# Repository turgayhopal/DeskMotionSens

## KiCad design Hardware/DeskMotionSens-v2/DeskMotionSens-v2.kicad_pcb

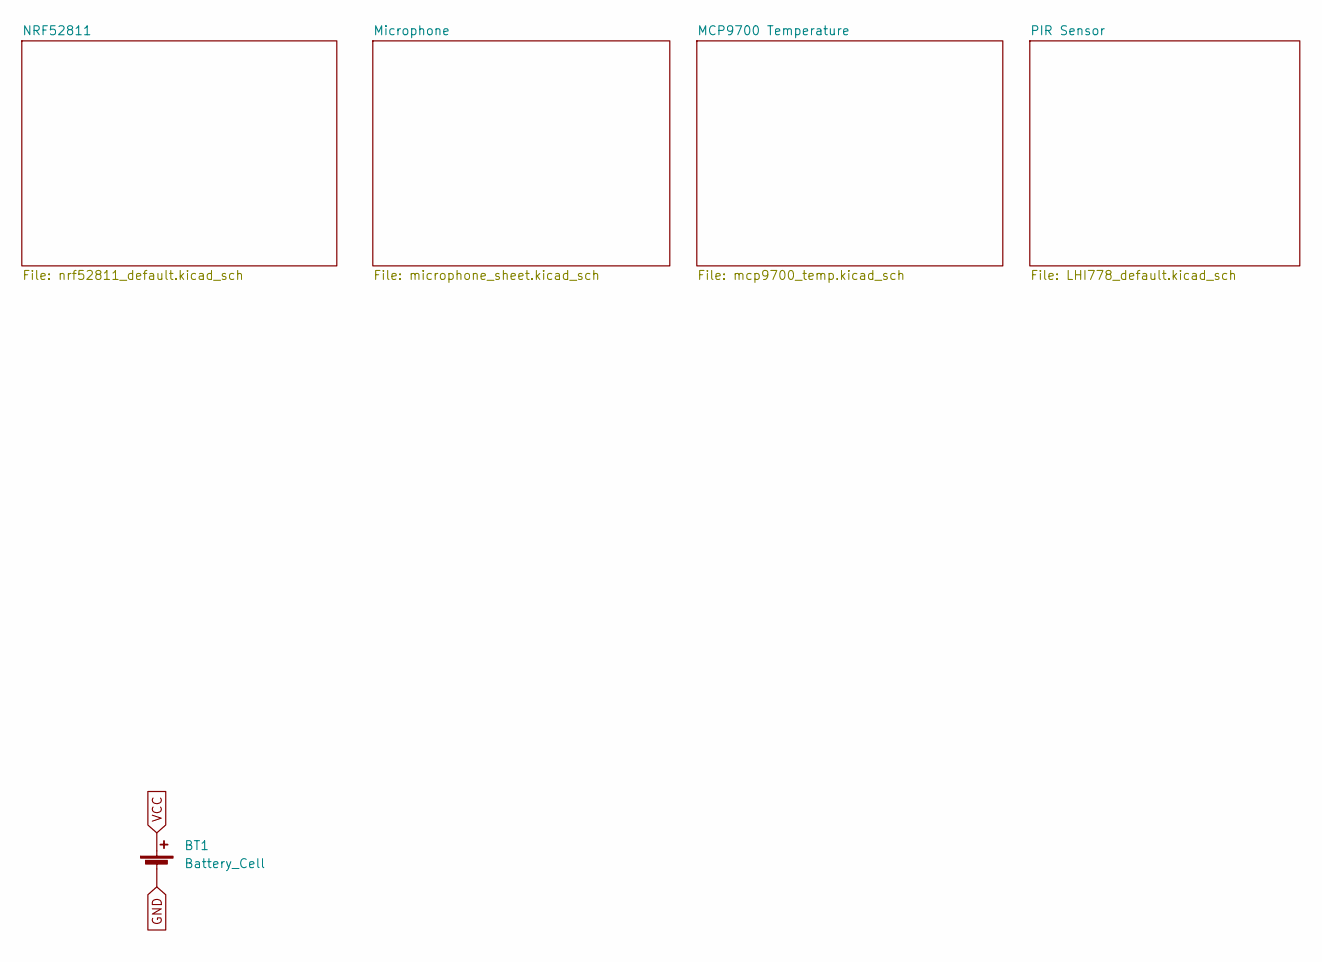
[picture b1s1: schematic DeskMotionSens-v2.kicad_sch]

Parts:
BT1: Battery_Cell; BatteryHolder_Keystone_1058_1x2032

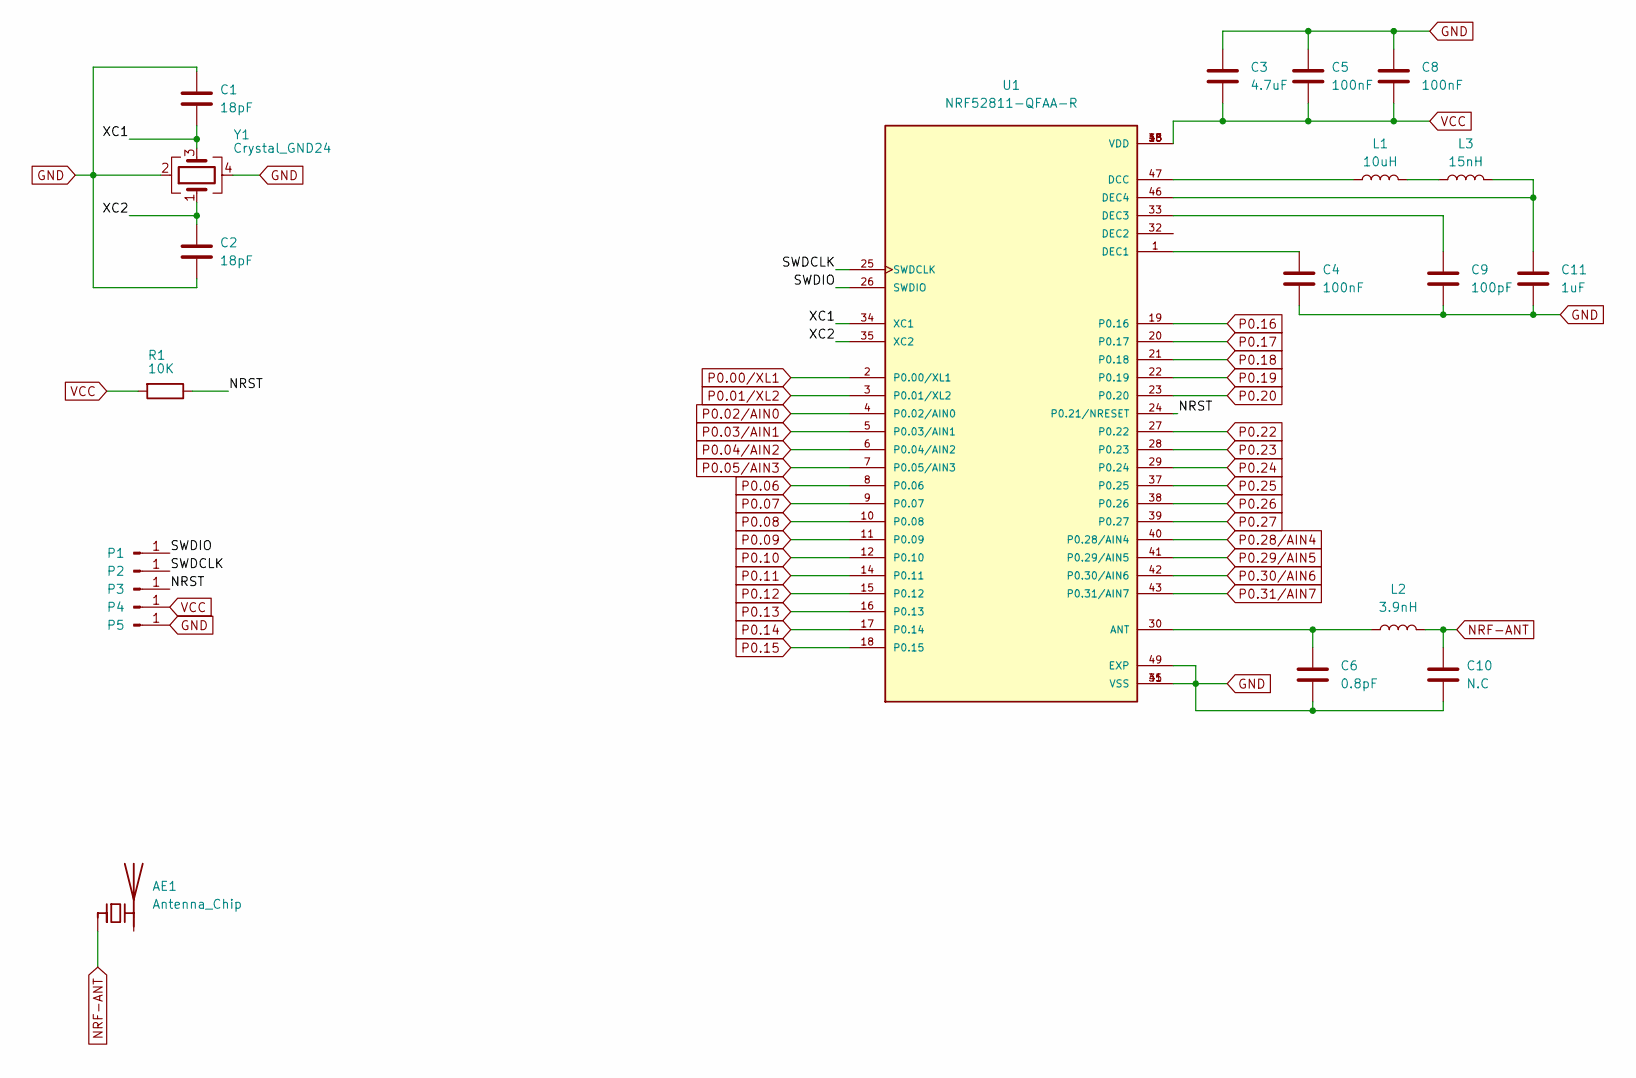
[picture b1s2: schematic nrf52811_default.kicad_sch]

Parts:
AE1: Antenna_Chip; Johanson_2450AT18x100
C1, C2: 18pF; C_0402_1005Metric
C3: 4.7uF; C_0402_1005Metric
C4, C5, C8: 100nF; C_0402_1005Metric
C6: 0.8pF; C_0402_1005Metric
C9: 100pF; C_0402_1005Metric
C10: N.C; C_0402_1005Metric
C11: 1uF; C_0402_1005Metric
L1: 10uH; C_0603_1608Metric
L2: 3.9nH; C_0603_1608Metric
L3: 15nH; C_0603_1608Metric
P1, P2, P3, P4, P5: Conn_01x01_Male; TestPoint_Pad_D1.0mm
R1: 10K; R_0402_1005Metric
U1: NRF52811-QFAA-R; QFN40P600X600X90-49N; PARTREV 1.0
Y1: Crystal_GND24; Crystal_SMD_3225-4Pin_3.2x2.5mm

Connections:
/NRF52811/NRST: P3.1, R1.1, U1.24 (P0.21/NRESET); also elsewhere on the board
/NRF52811/SWDCLK: P2.1, U1.25 (SWDCLK); also elsewhere on the board
/NRF52811/SWDIO: P1.1, U1.26 (SWDIO); also elsewhere on the board
/NRF52811/XC1: C1.1, U1.34 (XC1), Y1.3; also elsewhere on the board
/NRF52811/XC2: C2.2, U1.35 (XC2), Y1.1; also elsewhere on the board
GND: C1.2, C2.1, C3.1, C4.2, C5.1, C6.2, C8.1, C9.2, C10.2, C11.2, P5.1, U1.31 (VSS), U1.45 (VSS), U1.49 (EXP), Y1.2, Y1.4; also elsewhere on the board
NRF-ANT: AE1.1 (FEED), C10.1, L2.2
unnamed 7: C4.1, U1.1 (DEC1); also elsewhere on the board
unnamed 8: C6.1, L2.1, U1.30 (ANT); also elsewhere on the board
unnamed 9: C9.1, U1.33 (DEC3); also elsewhere on the board
unnamed 10: C11.1, L3.2, U1.46 (DEC4); also elsewhere on the board
unnamed 11: L1.1, U1.47 (DCC); also elsewhere on the board
unnamed: L1.2, L3.1
VCC: C3.2, C5.2, C8.2, P4.1, R1.2, U1.13 (VDD), U1.36 (VDD), U1.48 (VDD); also elsewhere on the board

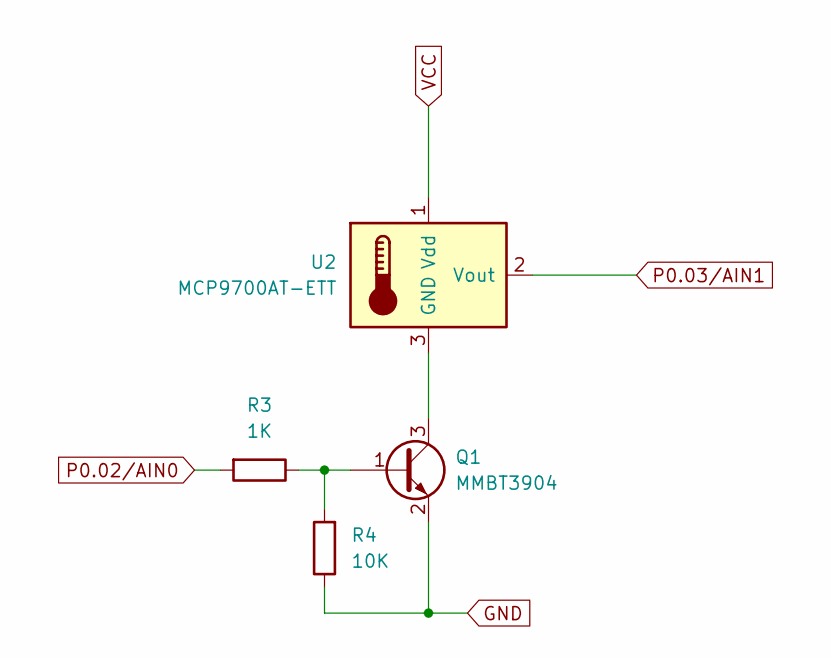
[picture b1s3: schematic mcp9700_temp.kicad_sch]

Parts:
Q1: MMBT3904; SOT-23
R3: 1K; R_0402_1005Metric
R4: 10K; R_0402_1005Metric
U2: MCP9700AT-ETT; SOT-23

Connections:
GND: Q1.2 (E), R4.1; also elsewhere on the board
unnamed: Q1.1 (B), R3.1, R4.2
unnamed: Q1.3 (C), U2.3 (GND)
P0.02/AIN0: R3.2; also elsewhere on the board
P0.03/AIN1: U2.2 (Vout); also elsewhere on the board
VCC: U2.1 (Vdd); also elsewhere on the board

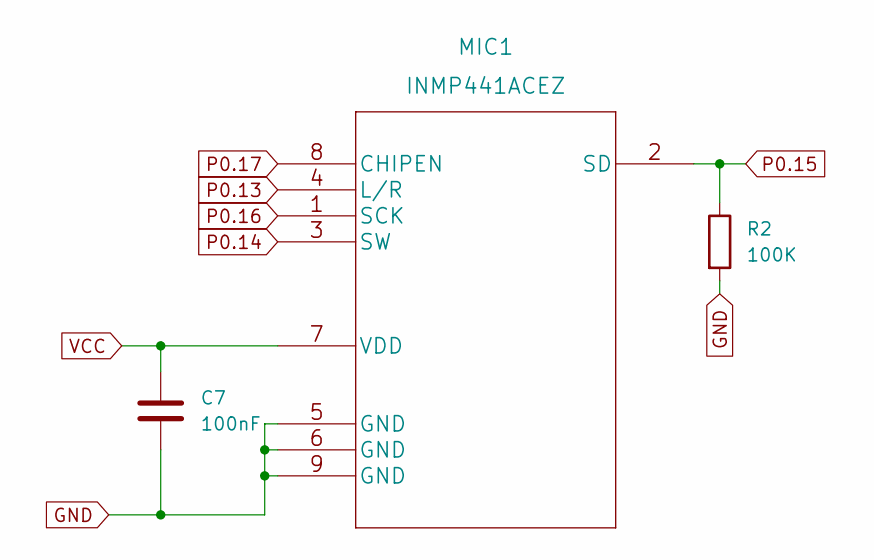
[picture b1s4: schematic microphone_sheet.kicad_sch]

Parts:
C7: 100nF; C_0402_1005Metric
MIC1: INMP441ACEZ
R2: 100K; R_0402_1005Metric

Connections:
GND: C7.1, MIC1.5 (GND), MIC1.6 (GND), MIC1.9 (GND), R2.2; also elsewhere on the board
P0.13: MIC1.4 (L/R); also elsewhere on the board
P0.14: MIC1.3 (SW); also elsewhere on the board
P0.15: MIC1.2 (SD), R2.1; also elsewhere on the board
P0.16: MIC1.1 (SCK); also elsewhere on the board
P0.17: MIC1.8 (CHIPEN); also elsewhere on the board
VCC: C7.2, MIC1.7 (VDD); also elsewhere on the board

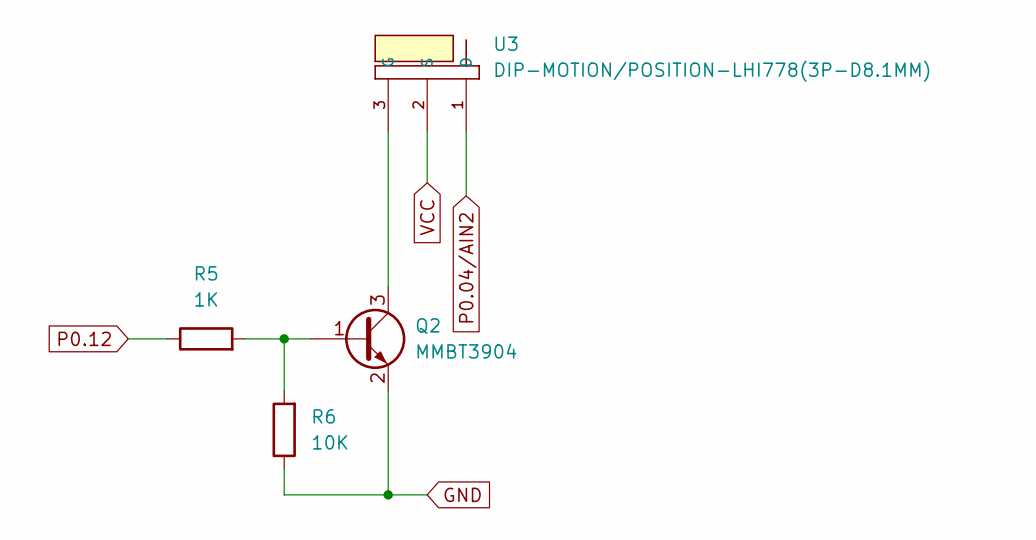
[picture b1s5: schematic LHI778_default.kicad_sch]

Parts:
Q2: MMBT3904; SOT-23
R5: 1K; R_0402_1005Metric
R6: 10K; R_0402_1005Metric
U3: DIP-MOTION/POSITION-LHI778(3P-D8.1MM); SNR3-D8.1XH4.2MM; MPN LHI778

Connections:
GND: Q2.2 (E), R6.1; also elsewhere on the board
unnamed: Q2.1 (B), R5.2, R6.2
unnamed: Q2.3 (C), U3.3 (G)
P0.04/AIN2: U3.1 (D); also elsewhere on the board
P0.12: R5.1; also elsewhere on the board
VCC: U3.2 (S); also elsewhere on the board

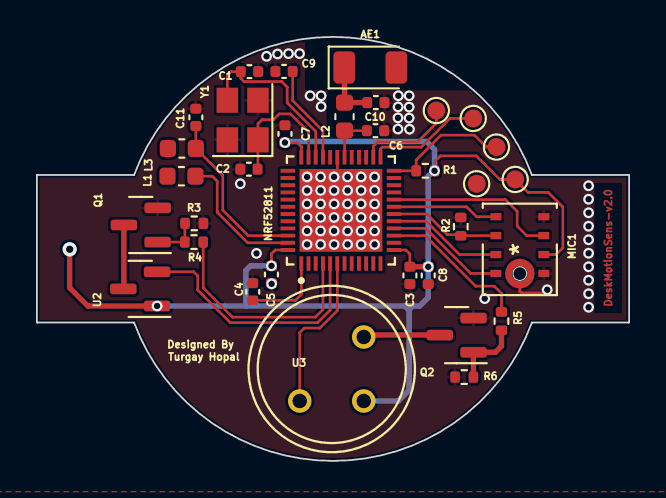
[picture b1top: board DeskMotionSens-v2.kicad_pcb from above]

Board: 2 copper layers, 32.9 x 23.6 mm, 34 parts (1 on the bottom side), 27 nets.

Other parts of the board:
Batterry: Battery_Cell; BatteryHolder_Keystone_1058_1x2032
NRF52811: NRF52811-QFAA-R; QFN40P600X600X90-49N

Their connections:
/NRF52811/NRST: NRF52811.24 (P0.21/NRESET); also elsewhere on the board
/NRF52811/SWDCLK: NRF52811.25 (SWDCLK); also elsewhere on the board
/NRF52811/SWDIO: NRF52811.26 (SWDIO); also elsewhere on the board
/NRF52811/XC1: NRF52811.34 (XC1); also elsewhere on the board
/NRF52811/XC2: NRF52811.35 (XC2); also elsewhere on the board
GND: Batterry.2 (-), NRF52811.31 (VSS), NRF52811.45 (VSS), NRF52811.49 (EXP); also elsewhere on the board
unnamed 7: NRF52811.1 (DEC1); also elsewhere on the board
unnamed 8: NRF52811.30 (ANT); also elsewhere on the board
unnamed 9: NRF52811.33 (DEC3); also elsewhere on the board
unnamed 10: NRF52811.46 (DEC4); also elsewhere on the board
unnamed 11: NRF52811.47 (DCC); also elsewhere on the board
P0.02/AIN0: NRF52811.4 (P0.02/AIN0); also elsewhere on the board
P0.03/AIN1: NRF52811.5 (P0.03/AIN1); also elsewhere on the board
P0.04/AIN2: NRF52811.6 (P0.04/AIN2); also elsewhere on the board
P0.12: NRF52811.15 (P0.12); also elsewhere on the board
P0.13: NRF52811.16 (P0.13); also elsewhere on the board
P0.14: NRF52811.17 (P0.14); also elsewhere on the board
P0.15: NRF52811.18 (P0.15); also elsewhere on the board
P0.16: NRF52811.19 (P0.16); also elsewhere on the board
P0.17: NRF52811.20 (P0.17); also elsewhere on the board
VCC: Batterry.1 (+), NRF52811.13 (VDD), NRF52811.36 (VDD), NRF52811.48 (VDD); also elsewhere on the board

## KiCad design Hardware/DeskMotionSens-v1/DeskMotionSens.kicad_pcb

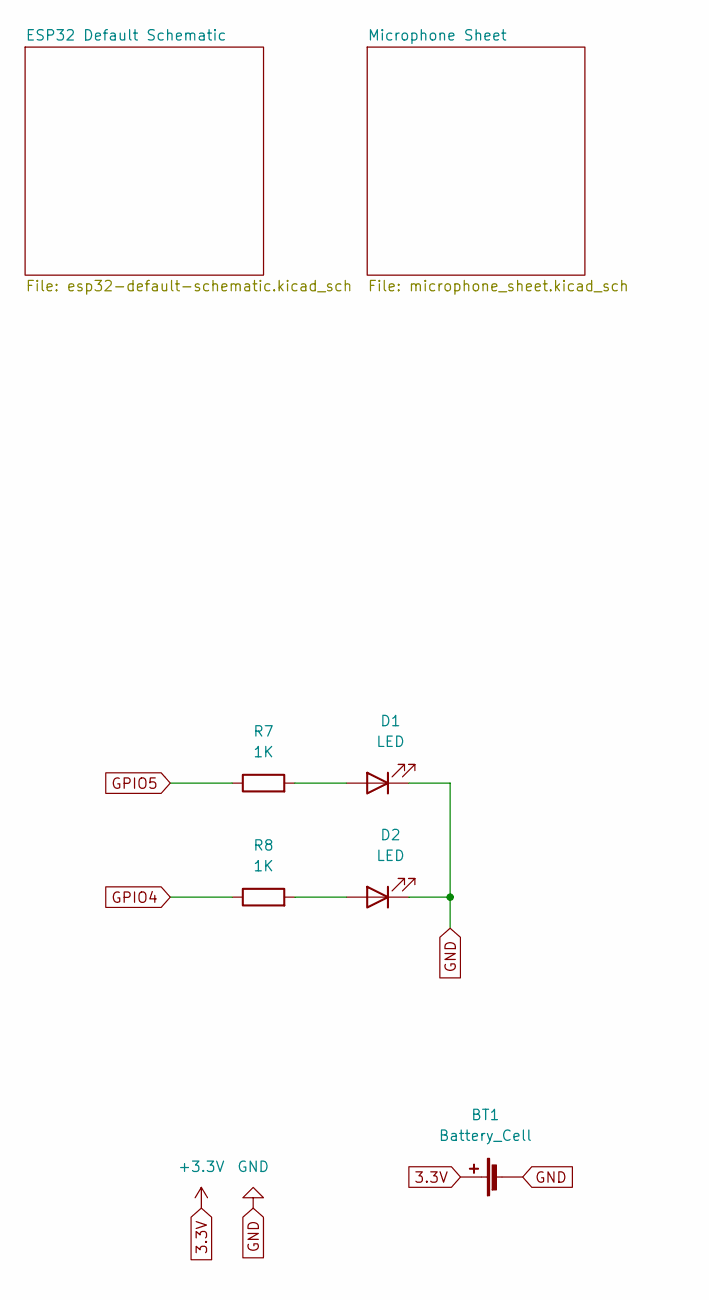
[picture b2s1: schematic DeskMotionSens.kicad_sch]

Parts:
BT1: Battery_Cell; BatteryHolder_Keystone_1058_1x2032
D1, D2: LED; LED_0402_1005Metric
R7, R8: 1K; R_0402_1005Metric

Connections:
3.3V: BT1.1 (+); also elsewhere on the board
GND: BT1.2 (-), D1.1 (K), D2.1 (K); also elsewhere on the board
GPIO4: R8.1; also elsewhere on the board
GPIO5: R7.1; also elsewhere on the board
unnamed: D1.2 (A), R7.2
unnamed: D2.2 (A), R8.2

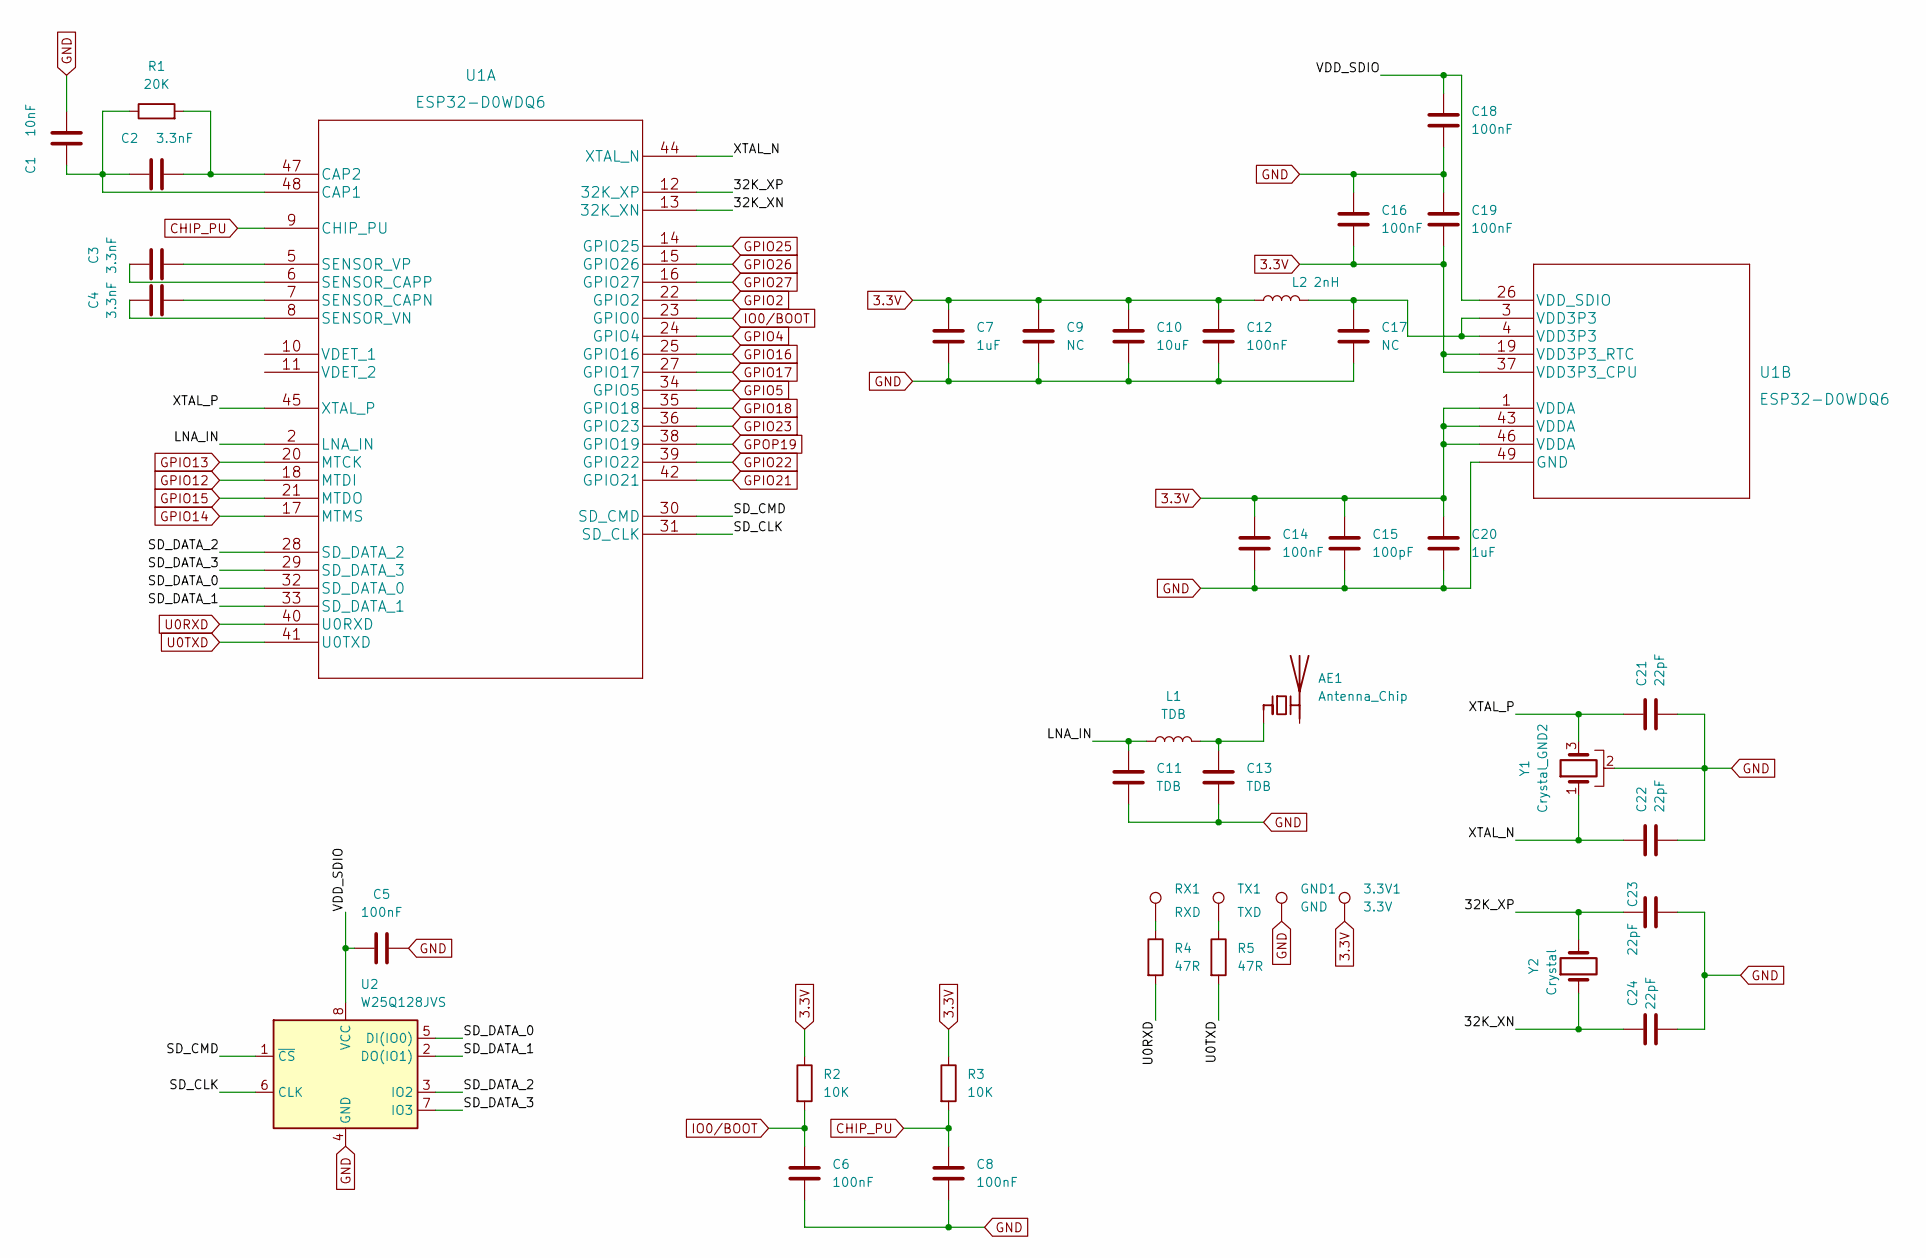
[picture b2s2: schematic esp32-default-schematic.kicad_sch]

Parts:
3.3V1: 3.3V; TestPoint_Pad_D1.0mm
AE1: Antenna_Chip; Johanson_2450AT18x100
C1: 10nF; C_0402_1005Metric
C2, C3, C4: 3.3nF; C_0402_1005Metric
C5, C6, C8, C12, C14, C16, C18, C19: 100nF; C_0402_1005Metric
C7, C20: 1uF; C_0402_1005Metric
C9, C17: NC; C_0402_1005Metric
C10: 10uF; C_0402_1005Metric
C11, C13: TDB; C_0402_1005Metric
C15: 100pF; C_0402_1005Metric
C21, C22, C23, C24: 22pF; C_0402_1005Metric
GND1: GND; TestPoint_Pad_D1.0mm
L1: TDB; L_0603_1608Metric
L2: 2nH; L_0603_1608Metric
R1: 20K; R_0402_1005Metric
R2, R3: 10K; R_0402_1005Metric
R4, R5: 47R; R_0402_1005Metric
RX1: RXD; TestPoint_Pad_D1.0mm
TX1: TXD; TestPoint_Pad_D1.0mm
U1: ESP32-D0WDQ6
U2: W25Q128JVS; SOIC-8_5.23x5.23mm_P1.27mm
Y1: Crystal_GND2; Crystal_SMD_Abracon_ABM8G-4Pin_3.2x2.5mm
Y2: Crystal; Crystal_SMD_EuroQuartz_EQ161-2Pin_3.2x1.5mm

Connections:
3.3V: 3.3V1.1, C7.1, C9.1, C10.1, C12.1, C14.1, C15.1, C16.2, C19.2, C20.1, L2.1, R2.1, R3.1, U1.1 (VDDA), U1.19 (VDD3P3_RTC), U1.37 (VDD3P3_CPU), U1.43 (VDDA), U1.46 (VDDA); also elsewhere on the board
/ESP32 Default Schematic/32K_XN: C24.1, U1.13 (32K_XN), Y2.1
/ESP32 Default Schematic/32K_XP: C23.1, U1.12 (32K_XP), Y2.2
/ESP32 Default Schematic/LNA_IN: C11.1, L1.1, U1.2 (LNA_IN)
/ESP32 Default Schematic/SD_CLK: U1.31 (SD_CLK), U2.6 (CLK)
/ESP32 Default Schematic/SD_CMD: U1.30 (SD_CMD), U2.1 (~CS)
/ESP32 Default Schematic/SD_DATA_0: U1.32 (SD_DATA_0), U2.5 (DI(IO0))
/ESP32 Default Schematic/SD_DATA_1: U1.33 (SD_DATA_1), U2.2 (DO(IO1))
/ESP32 Default Schematic/SD_DATA_2: U1.28 (SD_DATA_2), U2.3 (IO2)
/ESP32 Default Schematic/SD_DATA_3: U1.29 (SD_DATA_3), U2.7 (IO3)
/ESP32 Default Schematic/VDD_SDIO: C5.1, C18.1, U1.26 (VDD_SDIO), U2.8 (VCC)
/ESP32 Default Schematic/XTAL_N: C22.1, U1.44 (XTAL_N), Y1.1
/ESP32 Default Schematic/XTAL_P: C21.1, U1.45 (XTAL_P), Y1.3
CHIP_PU: C8.1, R3.2, U1.9 (CHIP_PU)
GND: C1.2, C5.2, C6.2, C7.2, C8.2, C9.2, C10.2, C11.2, C12.2, C13.1, C14.2, C15.2, C16.1, C17.2, C18.2, C19.1, C20.2, C21.2, C22.2, C23.2, C24.2, GND1.1, U1.49 (GND), U2.4 (GND), Y1.2; also elsewhere on the board
GPIO2: U1.22 (GPIO2)
GPIO4: U1.24 (GPIO4); also elsewhere on the board
GPIO5: U1.34 (GPIO5); also elsewhere on the board
GPIO12: U1.18 (MTDI); also elsewhere on the board
GPIO13: U1.20 (MTCK); also elsewhere on the board
GPIO14: U1.17 (MTMS); also elsewhere on the board
GPIO15: U1.21 (MTDO)
GPIO16: U1.25 (GPIO16)
GPIO17: U1.27 (GPIO17)
GPIO18: U1.35 (GPIO18)
GPIO21: U1.42 (GPIO21)
GPIO22: U1.39 (GPIO22)
GPIO23: U1.36 (GPIO23)
GPIO25: U1.14 (GPIO25)
GPIO26: U1.15 (GPIO26); also elsewhere on the board
GPIO27: U1.16 (GPIO27); also elsewhere on the board
GPOP19: U1.38 (GPIO19)
IO0/BOOT: C6.1, R2.2, U1.23 (GPIO0)
unnamed: AE1.1 (FEED), C13.2, L1.2
unnamed: C1.1, C2.1, R1.1, U1.48 (CAP1)
unnamed: C2.2, R1.2, U1.47 (CAP2)
unnamed: C3.1, U1.5 (SENSOR_VP)
unnamed: C3.2, U1.6 (SENSOR_CAPP)
unnamed: C4.1, U1.7 (SENSOR_CAPN)
unnamed: C4.2, U1.8 (SENSOR_VN)
unnamed: C17.1, L2.2, U1.3 (VDD3P3), U1.4 (VDD3P3)
unnamed 43: R4.1, RX1.1; also elsewhere on the board
unnamed 44: R5.1, TX1.1; also elsewhere on the board
U0RXD: R4.2, U1.40 (U0RXD)
U0TXD: R5.2, U1.41 (U0TXD)

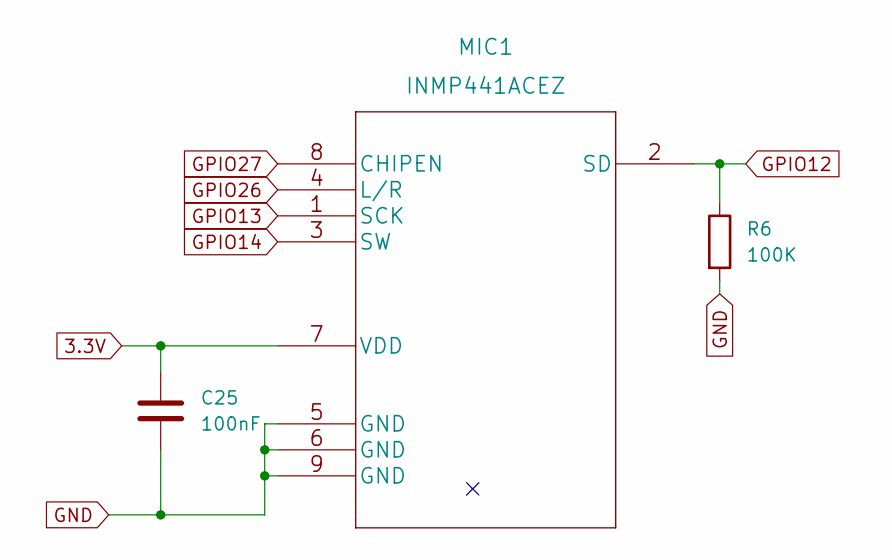
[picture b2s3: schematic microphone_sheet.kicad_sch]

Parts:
C25: 100nF; C_0402_1005Metric
MIC1: INMP441ACEZ
R6: 100K; R_0402_1005Metric

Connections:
3.3V: C25.2, MIC1.7 (VDD); also elsewhere on the board
GND: C25.1, MIC1.5 (GND), MIC1.6 (GND), MIC1.9 (GND), R6.2; also elsewhere on the board
GPIO12: MIC1.2 (SD), R6.1; also elsewhere on the board
GPIO13: MIC1.1 (SCK); also elsewhere on the board
GPIO14: MIC1.3 (SW); also elsewhere on the board
GPIO26: MIC1.4 (L/R); also elsewhere on the board
GPIO27: MIC1.8 (CHIPEN); also elsewhere on the board

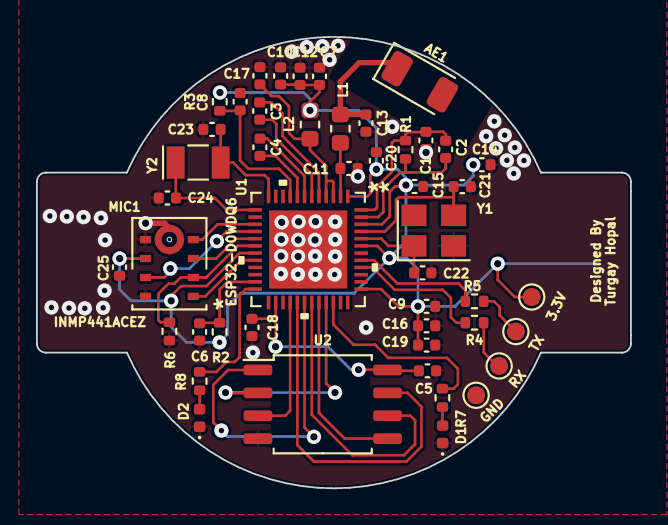
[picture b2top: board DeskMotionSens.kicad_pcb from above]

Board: 2 copper layers, 33.0 x 25.1 mm, 48 parts (1 on the bottom side), 37 nets.

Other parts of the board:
3.3V: 3.3V; TestPoint_Pad_D1.0mm
GND: GND; TestPoint_Pad_D1.0mm
RX: RXD; TestPoint_Pad_D1.0mm
TX: TXD; TestPoint_Pad_D1.0mm

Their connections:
3.3V: 3.3V.1; also elsewhere on the board
GND: GND.1; also elsewhere on the board
unnamed 43: RX.1; also elsewhere on the board
unnamed 44: TX.1; also elsewhere on the board

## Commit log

2022-07-25 Add new Board

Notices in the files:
parts and their libraries:
Copyright 2021 Accelerated Designs. All rights reserved.
